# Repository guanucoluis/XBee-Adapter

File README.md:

XBEE-Adapter
============

KiCad Files for XBee Regulated Adapter Board

KiCad Build: 2012-01-19 BZR 3256 Stable

http://thefragmentationparadox.blogspot.pt/2014/06/xbee-regulated-adapter-board.html

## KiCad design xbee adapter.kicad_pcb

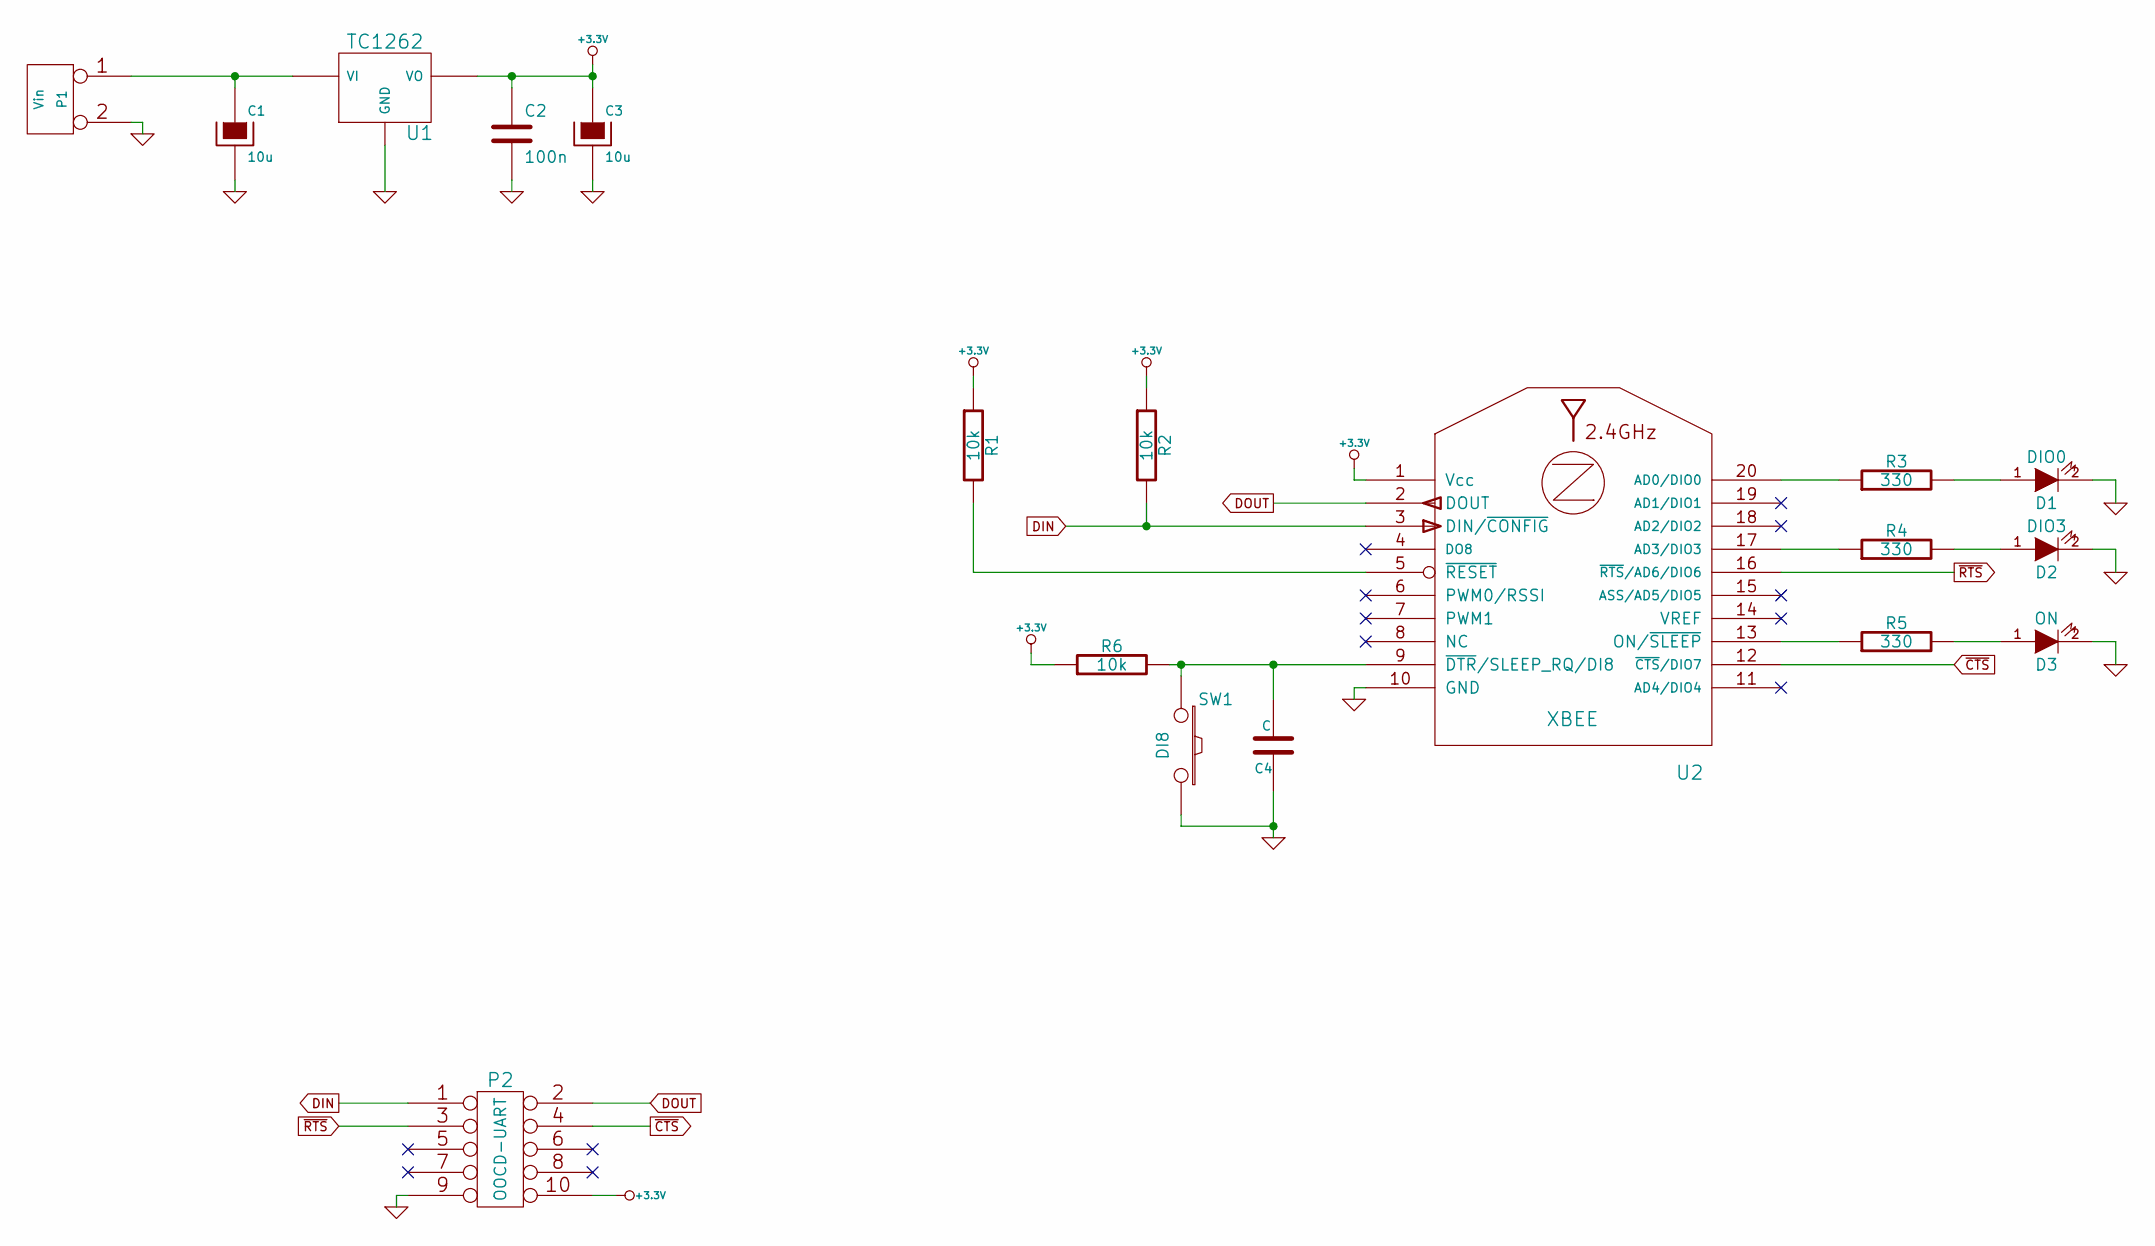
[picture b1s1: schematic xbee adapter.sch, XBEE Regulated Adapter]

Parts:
C1, C3: 10u
C2: 100n
C4: C
D1: DIO0
D2: DIO3
D3: ON
P1: Vin
P2: OOCD-UART
R1, R2, R6: 10k
R3, R4, R5: 330
SW1: DI8
U1: TC1262
U2: XBEE

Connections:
+3.3V: C2.1, C3.1, P2.10, R1.1, R2.1, R6.1, U1.3 (VO), U2.1 (Vcc)
DIN: P2.1, R2.2, U2.3 (DIN/~CONFIG)
DOUT: P2.2, U2.2 (DOUT)
GND: C1.2, C2.2, C3.2, C4.1, D1.2 (K), D2.2 (K), D3.2 (K), P1.2 (PM), P2.9, SW1.2, U1.2 (GND), U2.10 (GND)
unnamed: C4.2, R6.2, SW1.1, U2.9 (~DTR~/SLEEP_RQ/DI8)
unnamed: C1.1, P1.1, U1.1 (VI)
unnamed: R1.2, U2.5 (~RESET)
unnamed: R3.1, U2.20 (AD0/DIO0)
unnamed: D1.1 (A), R3.2
unnamed: D3.1 (A), R5.2
unnamed: R5.1, U2.13 (ON/~SLEEP)
unnamed: D2.1 (A), R4.2
unnamed: R4.1, U2.17 (AD3/DIO3)
~CTS: P2.4, U2.12 (~CTS~/DIO7)
~RTS: P2.3, U2.16 (~RTS~/AD6/DIO6)

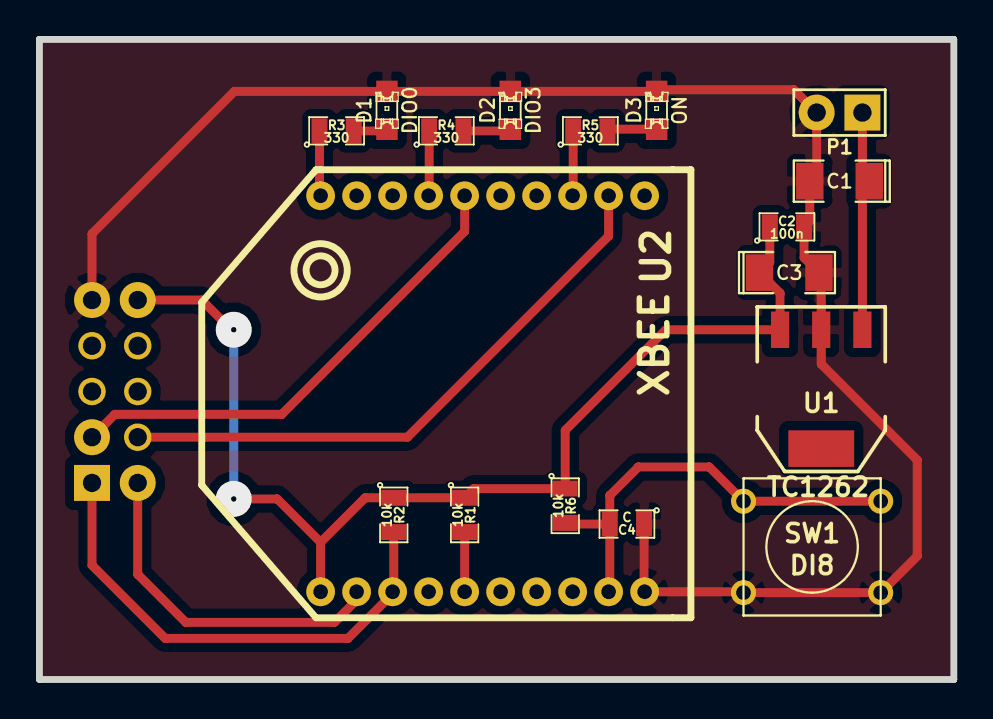
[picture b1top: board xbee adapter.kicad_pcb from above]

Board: 2 copper layers, 50.8 x 35.6 mm, 18 parts (1 on the bottom side), 15 nets.

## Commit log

2015-09-18 [XBEE] Primera versión para el PCB
2015-09-18 [XBEE] agrego archivos faltantes
2015-09-18 [XBEE] agrego esquemático en pdf
